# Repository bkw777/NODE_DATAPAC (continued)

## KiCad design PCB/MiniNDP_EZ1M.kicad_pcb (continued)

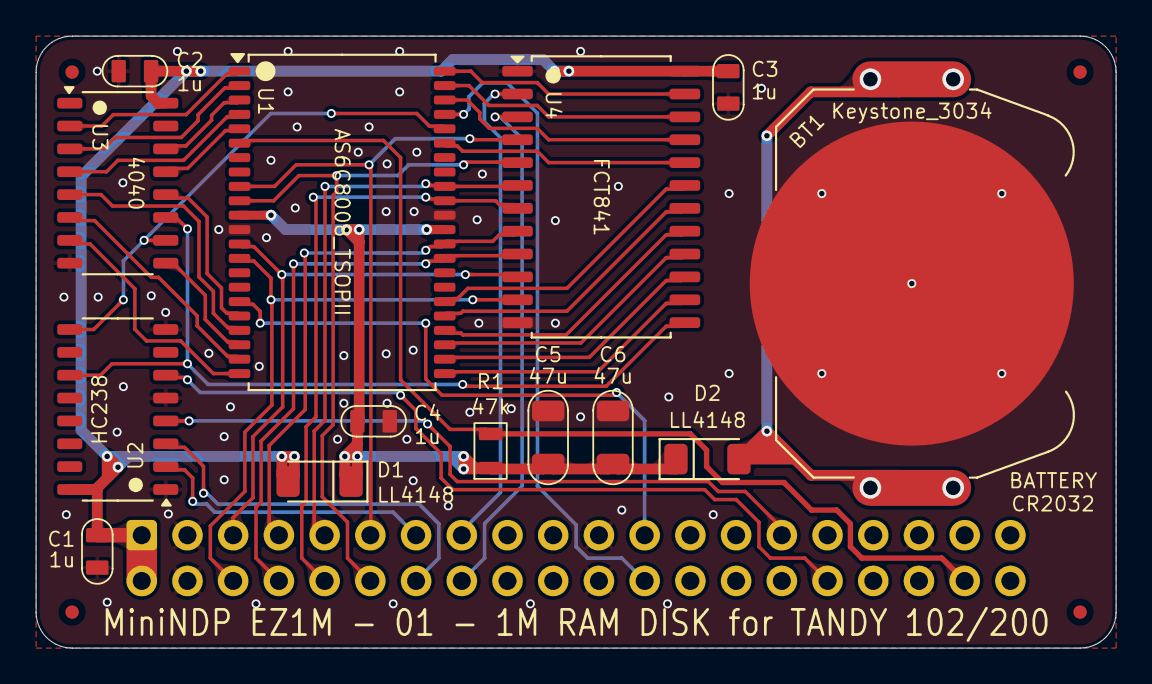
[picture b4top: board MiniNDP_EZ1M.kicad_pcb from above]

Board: 2 copper layers, 60.0 x 34.0 mm, 20 parts (1 on the bottom side), 43 nets.

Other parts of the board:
F2, F2#2, F3, F3#2: Fiducial_0.75_1.5

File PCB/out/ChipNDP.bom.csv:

"Reference","Value","Datasheet","Footprint","Qty","DNP","MPN","Description"
"BT1","Keystone_3031","datasheet/Keystone_3031.pdf","000_LOCAL:Keystone_3031","1","","Keystone 3031","Battery Retainer Coin, 10.0mm 1 Cell PC Pin"
"C1,C2,C3","1u","datasheets/CL21B105KAFNNNE.pdf","000_LOCAL:C_0805","3","","CL21B105KAFNNNE","CAP CER 1UF 25V X7R 0805"
"C4","47u","datasheets/TDK_MLCC_Cxxxx.pdf","000_LOCAL:C_1206","1","","C3216X5R1E476M160DC","CAP CER 47UF 25V X5R 1206"
"DA1","BAV70","datasheets/BAV70.pdf","000_LOCAL:SOT-23","1","","BAV70-7-F","DIODE ARRAY GP 75V 150MA SOT23-3"
"J1","Model_100_System_BUS","datasheets/TRS-80_Model_100_User_Guide.pdf","000_LOCAL:DIP-40_PCB","1","","920-0172-01","CONN HEADER VERT 40P 2.54MM"
"R1","47k","datasheets/sei-rmcf_rmcp.pdf","000_LOCAL:R_0805","1","","RMCF0805FT47K0","RES 47K OHM 1% 1/8W 0805"
"U1","AS6C8008_TSOPII","datasheets/AS6C8008.pdf","000_LOCAL:TSOP-II-44","1","","AS6C8008-55ZIN","IC SRAM 1Mx8 PARALLEL 5v TSOP-II-44"
"U2","HC238","datasheets/HC238.pdf","000_LOCAL:TSSOP-16","1","","74HC238PW,118","IC DECODER/DEMUX 1 X 3:8 16SO"
"U3","HC4040","datasheets/4040.pdf","000_LOCAL:TSSOP-16","1","","74HC4040PW,118","IC BINARY COUNTER 12-BIT 16SO"
"U4","ABT841","datasheets/sn54abt841.pdf","000_LOCAL:TSSOP-24_4.4x7.8mm_P0.65mm","1","","SN74ABT841APW","IC 10BIT LATCH 3-STATE 24-SOIC"
